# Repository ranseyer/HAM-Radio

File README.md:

View this project on [CADLAB.io](https://cadlab.io/project/23326). 

# HAM-Radio

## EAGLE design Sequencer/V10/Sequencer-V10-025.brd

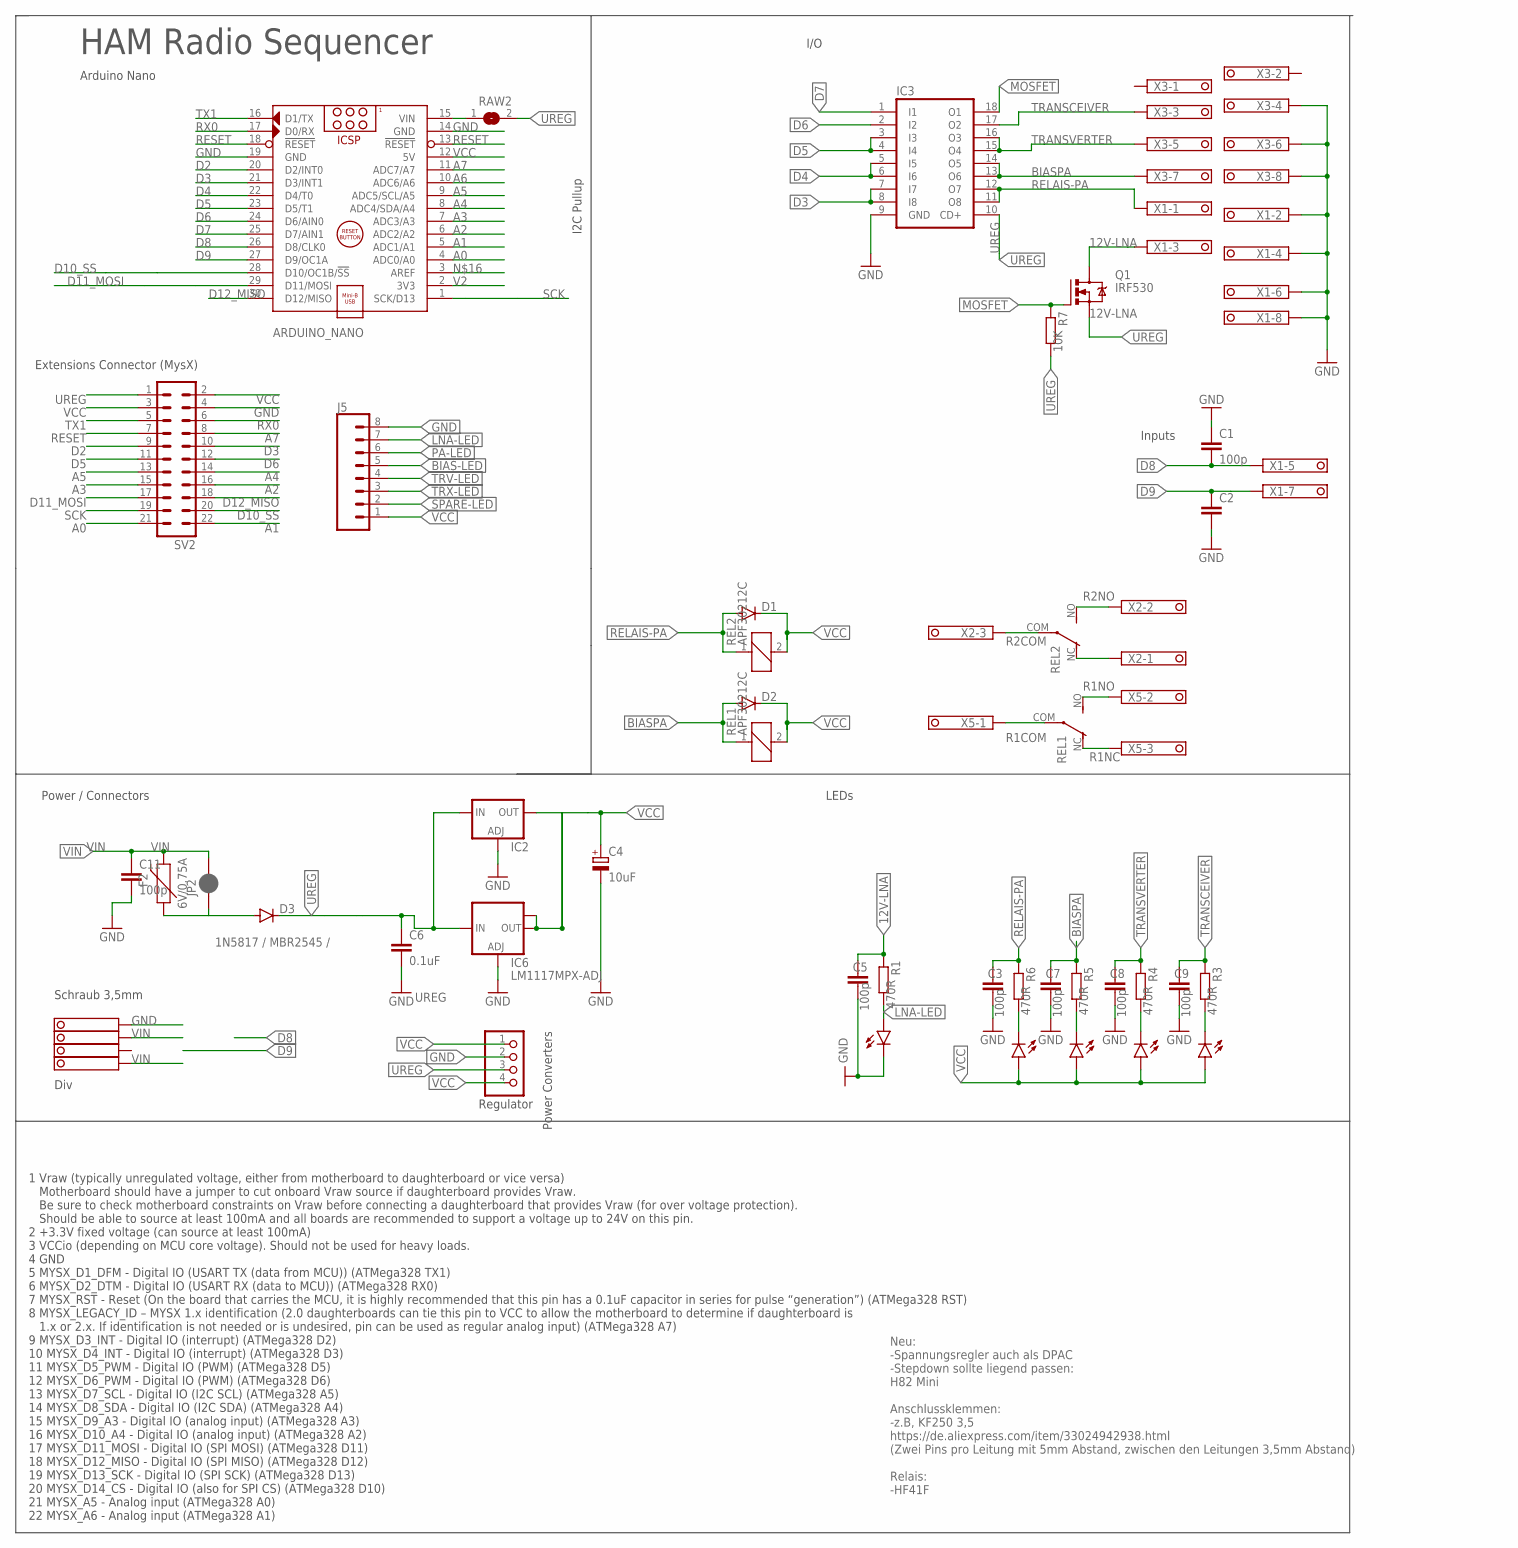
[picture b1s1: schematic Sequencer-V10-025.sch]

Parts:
ARDUINO_NANO: ARDUINO_NANO_OHNE-BOHR; ARDUINO_NANO
C1, C3, C5, C7, C8, C9, C11: 100p; C025-025X050
C2: C-EU025-025X050; C025-025X050
C4: 10uF; E3,5-8
C6: 0.1uF; C050-024X044
D1, D2: DIODE-D-2.5; D-2.5
D3: 1N5817 / MBR2545 /; D-7.5
F2: 6V/0.75A; 1206
IC2: LD117ADT50TR; DPACK
IC3: ULN2803A; DIL18
IC6: LM1117MPX-ADJ; SOT223
J5: CONN_08LOCK; 1X08_LOCK
JP2: JUMPER-SMT_2_NC_PASTE_NO-SILK; SMT-JUMPER_2_NC_PASTE_NO-SILK
LED-BIAS: LED3MM
LED-LNA: LED3MM
LED-PA: LED3MM
LED-TRV: LED3MM
LED-TRX: LED3MM
Q1: IRF530; TO220BV
R1, R3, R4, R5, R6: 470R; 0207/7
R7: 10K; 0207/7
RAW2: SJ
REL1, REL2: APF30212C
STEPDWN: PINHD-1X04_2.54-S; 1X04-S
SV2: MA11-2
X1, X3: MARTIN8X2-1751303; 1751303
X2, X5: MARTIN3X2-1751303175L303-3; 1751303-3
X4: 1751264

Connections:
12V-LNA: C5.1, Q1.D, R1.1, X1.11
A0: ARDUINO_NANO.4 (ADC0/A0), SV2.21
A1: ARDUINO_NANO.5 (ADC1/A1), SV2.22
A2: ARDUINO_NANO.6 (ADC2/A2), SV2.16
A3: ARDUINO_NANO.7 (ADC3/A3), SV2.15
A4: ARDUINO_NANO.8 (ADC4/SDA/A4), SV2.14
A5: ARDUINO_NANO.9 (ADC5/SCL/A5), SV2.13
A6: ARDUINO_NANO.10 (ADC6/A6)
A7: ARDUINO_NANO.11 (ADC7/A7), SV2.8
BIAS-LED: J5.5, LED-BIAS.K (C), R5.2
BIASPA: C7.1, D2.A, IC3.13 (O6), IC3.14 (O5), R5.1, REL1.1, X3.15
D2: ARDUINO_NANO.20 (D2/INT0), SV2.9
D3: ARDUINO_NANO.21 (D3/INT1), IC3.7 (I7), IC3.8 (I8), SV2.10
D4: ARDUINO_NANO.22 (D4/T0), IC3.5 (I5), IC3.6 (I6)
D5: ARDUINO_NANO.23 (D5/T1), IC3.3 (I3), IC3.4 (I4), SV2.11
D6: ARDUINO_NANO.24 (D6/AIN0), IC3.2 (I2), SV2.12
D7: ARDUINO_NANO.25 (D7/AIN1), IC3.1 (I1)
D8: ARDUINO_NANO.26 (D8/CLK0), C1.2, X1.13
D9: ARDUINO_NANO.27 (D9/OC1A), C2.1, X1.15
D10_SS: ARDUINO_NANO.28 (D10/OC1B/!SS), SV2.20
D11_MOSI: ARDUINO_NANO.29 (D11/MOSI), SV2.17
D12_MISO: ARDUINO_NANO.30 (D12/MISO), SV2.18
GND: ARDUINO_NANO.14 (GND), ARDUINO_NANO.19 (GND), C1.1, C2.2, C3.2, C4.-, C5.2, C6.2, C7.2, C8.2, C9.2, C11.2, IC2.1 (ADJ), IC3.9 (GND), IC6.1 (ADJ), J5.8, LED-LNA.K (C), STEPDWN.2, SV2.4, X1.10, X1.12, X1.14, X1.16, X3.12, X3.14, X3.16, X4.4
LNA-LED: J5.7, LED-LNA.A, R1.2
MOSFET: IC3.18 (O1), Q1.G, R7.1
unnamed: D3.A, F2.1, JP2.1
PA-LED: J5.6, LED-PA.K (C), R6.2
R1COM: REL1.COM, X5.1
R1NC: REL1.NC (O), X5.3
R1NO: REL1.NO (S), X5.2
R2COM: REL2.COM, X2.3
R2NC: REL2.NC (O), X2.1
R2NO: REL2.NO (S), X2.2
RAW1: ARDUINO_NANO.15 (VIN), RAW2.1
RELAIS-PA: C3.1, D1.A, IC3.11 (O8), IC3.12 (O7), R6.1, REL2.1, X1.9
RESET: ARDUINO_NANO.13 (!RESET), ARDUINO_NANO.18 (!RESET), SV2.7
RX0: ARDUINO_NANO.17 (D0/RX), SV2.6
SCK: ARDUINO_NANO.1 (SCK/D13), SV2.19
SPARE-LED: J5.2
TRANSCEIVER: C9.1, IC3.17 (O2), R3.1, X3.11
TRANSVERTER: C8.1, IC3.15 (O4), IC3.16 (O3), R4.1, X3.13
TRV-LED: J5.4, LED-TRV.K (C), R4.2
TRX-LED: J5.3, LED-TRX.K (C), R3.2
TX1: ARDUINO_NANO.16 (D1/TX), SV2.5
UREG: C6.1, D3.C, IC2.3 (IN), IC3.10 (CD+), IC6.3 (IN), Q1.S, R7.2, RAW2.2, STEPDWN.3, SV2.1
V2: ARDUINO_NANO.2 (3V3)
VCC: ARDUINO_NANO.12 (5V), C4.+, D1.C, D2.C, IC2.4 (OUT), IC6.2 (OUT), IC6.TAB (OUT1), J5.1, LED-BIAS.A, LED-PA.A, LED-TRV.A, LED-TRX.A, REL1.2, REL2.2, STEPDWN.1, STEPDWN.4, SV2.2, SV2.3
VIN: C11.1, F2.2, JP2.2, X4.1, X4.3

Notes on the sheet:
HAM Radio Sequencer
Arduino Nano
Div
Neu: -Spannungsregler auch als DPAC -Stepdown sollte liegend passen: H82 Mini Anschlussklemmen: -z.B, KF250 3,5 https://de.aliexpress.com/item/33024942938.html (Zwei Pins pro Leitung mit 5mm Abstand, zwischen den Leitungen 3,5mm Abstand) Relais: -HF41F
Power Converters
I/O
Schraub 3,5mm
Regulator
1 Vraw (typically unregulated voltage, either from motherboard to daughterboard or vice versa) Motherboard should have a jumper to cut onboard Vraw source if daughterboard provides Vraw. Be sure to check motherboard constraints on Vraw before connecting a daughterboard that provides Vraw (for over 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
I2C Pullup
Inputs
Extensions Connector (MysX)
Power / Connectors
LEDs

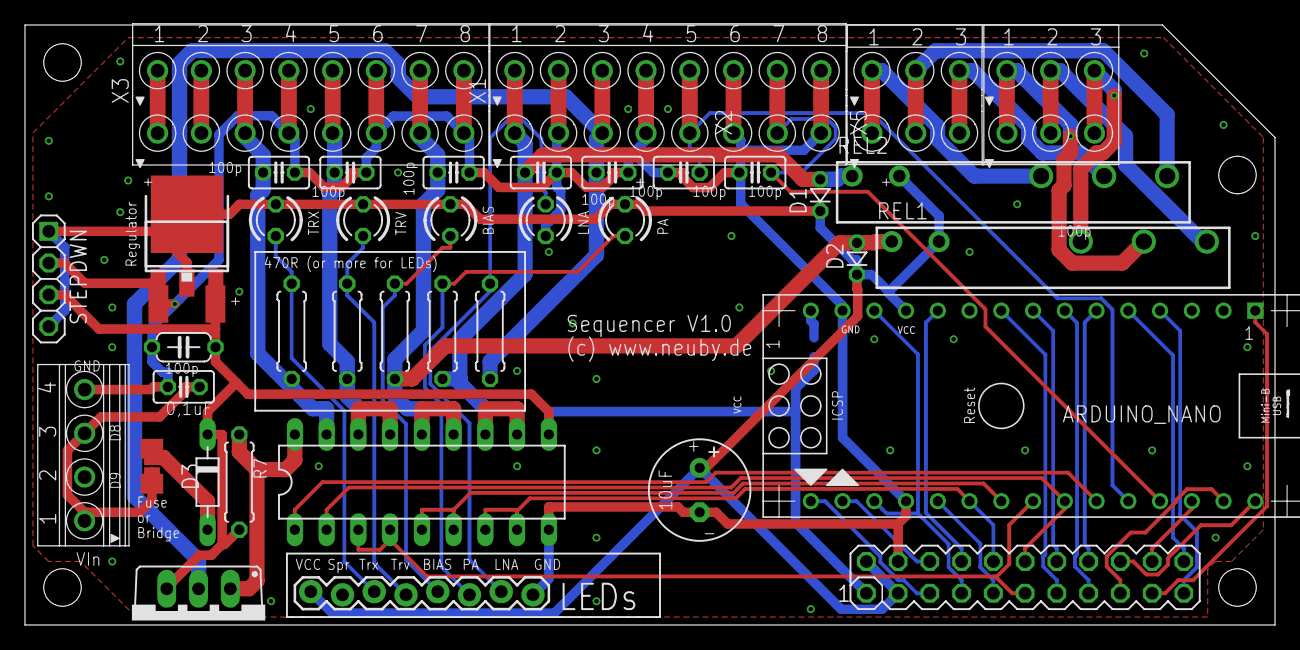
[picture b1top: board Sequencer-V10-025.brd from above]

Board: 2 copper layers, 100.0 x 48.0 mm, 42 parts (1 on the bottom side), 45 nets.

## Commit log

2020-01-12 Sequencer
2020-01-12 cleanup
2020-09-17 Backlink to CADLAB.io has been added.
2020-09-22 V02 Final
2021-02-03 Sequencer V1.0
2021-02-05 Fix MOSFET to UREG

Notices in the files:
parts and their libraries:
SparkFun-Fuses: Licensing: Creative Commons ShareAlike 4.0 International - https://creativecommons.org/licenses/by-sa/4.0
